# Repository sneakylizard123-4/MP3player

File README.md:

# MP3 Player

A pocket-sized music player I designed and built from scratch. It plays audio off a microSD card, tunes into FM radio, and can record through a MEMS microphone — all on one 50×70mm PCB with an OLED screen, RGB LEDs, and seventeen physical buttons.

It's built around an STM32H743 running at 480MHz, and the audio comes out through a CS43131 DAC. The whole thing was designed in KiCad 10 and the firmware is C++ written with PlatformIO on ST's HAL.

## Why I built this

I wanted a music player that was actually *mine*. Phones sound great and all, but you can't change anything about them — the hardware is sealed up, there's no satisfying button to press, and the software only does what the manufacturer lets it do. I wanted real buttons, a screen, lights that react to the music, and firmware I could rewrite from scratch whenever I felt like it.

It also turned out to be the perfect excuse to practice the stuff I actually enjoy: PCB design, embedded firmware, and getting hardware interfaces to talk to each other.

I went with the STM32H743 because it has the RAM to buffer audio properly, enough peripherals for everything I wanted to add, and 480MHz of headroom so I never have to worry about it being slow.

## Pictures

 | 

## Features

**Audio**

* CS43131 high-res headphone DAC with a built-in amp
* Dedicated low-noise power rail just for the audio stuff
* 3.5mm headphone output
* Si4735 AM/FM radio receiver
* ICS-43434 I2S microphone for recording

**Storage & controls**

* microSD card over 4-bit SDMMC
* OLED display
* 17 buttons: a 3×3 matrix for navigation plus direct controls
* APA102 RGB LEDs

**Sensors**

* LSM6DSL 6-axis IMU
* BME680 temperature / humidity / pressure / gas sensor
* ISL29035 ambient light sensor
* DS3231M real-time clock

**Power**

* USB-C charging via a BQ24090DGQ Li-ion charger
* TPS613222ADBV boost converter for the 5V rail
* Separate digital and low-noise analog rails

## What the sensors actually do

None of these are needed to play music, but they're what turn this from "a box that plays audio" into something that notices the world around it:

* **LSM6DSL IMU** — motion and orientation. You could shake it to skip a track, flip it to mute, rotate the UI, or drive the LEDs off the beat.
* **BME680** — temperature, humidity, pressure, and VOC levels. Nice for showing environmental data on the OLED, and it can track air quality over time.
* **ISL29035** — how bright it is outside. Auto-adjusts the OLED brightness so it stays readable in daylight and saves battery at night.
* **DS3231M RTC** — keeps accurate time even when the player is off, for a clock on the display, recording timestamps, and maybe alarms later.

# Hardware

## Power

A single Li-ion cell powers everything, with separate rails for the digital side, the LEDs, and the analog audio. The charger (BQ24090DGQ) handles USB input, battery management, and has an NTC thermistor on the pack for temperature monitoring plus charge status LEDs. The boost converter (TPS613222ADBV) steps the battery up to 5V for the LEDs and peripherals, a TLV70233 LDO makes the 3.3V digital rail, and a TPS7A4701 low-noise LDO feeds the audio.

Power flow:

```
USB-C
  |
  +-- USBLC6 ESD protection
  |
  +-- BQ24090DGQ Li-ion charger
          |
          +-- Li-ion battery
                  |
                  +-- TPS613222ADBV boost converter
                  |       |
                  |       +-- 5V rail (LEDs and peripherals)
                  |
                  +-- TLV70233 LDO
                  |       |
                  |       +-- 3.3V digital rail
                  |
                  +-- TPS7A4701 low-noise LDO
                          |
                          +-- audio rail
```

The digital and audio rails are deliberately kept apart so switching noise from the boost converter doesn't end up in your headphones. The DAC gets its own clean regulator for the same reason.

## Schematic

The design is split across hierarchical KiCad sheets:

| Sheet        | File                  | Description                                  | Main Components                                        |
| ------------ | --------------------- | -------------------------------------------- | ------------------------------------------------------ |
| Root         | MP3player.kicad_sch   | Connections and system overview              | Power symbols, connectors, mounting holes              |
| STM32 Core   | stm32core.kicad_sch   | MCU and sensors                              | STM32H743, LSM6DSL, BME680, ISL29035, DS3231M          |
| Power        | power.kicad_sch       | Charging and regulation                      | BQ24090DGQ, TPS613222ADBV, TPS7A4701, TLV70233, USBLC6 |
| Audio        | audio.kicad_sch       | Headphone audio path                         | CS43131-CNZR                                           |
| Storage      | storage.kicad_sch     | Removable storage                            | MicroSD socket                                         |
| OLED UI      | oledui.kicad_sch      | Display and buttons                          | OLED, button matrix, GPIO controls                     |
| Radio        | radio.kicad_sch       | AM/FM receiver                               | Si4735-D60-GU                                          |
| Microphone   | microphone.kicad_sch  | Audio input                                  | ICS-43434 MEMS microphone                              |
| LED Spectrum | ledspectrum.kicad_sch | Visual audio display                         | APA102-2020 LEDs                                       |

## PCB

Six layers, 1.6mm thick, about 50×70mm. Internal power planes keep the distribution clean, and I paid attention to keeping the analog audio away from the digital and switching sections. The DAC sits right next to the headphone jack so the analog traces stay short, and the high-current paths around the charger and boost converter are kept tight with proper return paths.

# Assembly

Designed for standard SMT assembly. Here's how it goes together:

1. Apply solder paste with the stencil.
2. Place the small stuff — 0603 resistors and caps, ferrite beads, crystals.
3. Place the big ICs: STM32H743 (LQFP-100), CS43131, Si4735, power management, APA102 LEDs, sensors.
4. Reflow.
5. Check the fine-pitch parts for solder bridges.
6. Install connectors: USB-C, headphone jack, microSD socket, SMA antenna connectors, battery connector, debug headers.
7. Install the user-facing stuff: 17 tactile switches and the OLED connector.
8. Electrical checks — continuity, shorts, and verifying the power rails.
9. Flash the initial firmware over SWD.

## Firmware

The firmware is in `firmware/`, built with PlatformIO on the STM32 HAL. Right now it sets up the hardware: 480MHz clock from the 8MHz crystal via PLL, all the GPIO, the I2C/SPI/UART buses, the SD card interface, and the control pins. The fun part — actual playback, the UI, radio control, recording, and the LED effects — is still being written.

### Build and flash

You'll need PlatformIO (CLI or the VS Code extension) and an ST-Link, CMSIS-DAP, or J-Link debugger.

```bash
cd firmware
pio run
```

To flash over SWD:

```bash
pio run -t upload
```

# Bill of Materials

| Ref      | Part                 | Qty | Package   | Description                         |
| -------- | -------------------- | --- | --------- | ----------------------------------- |
| U4       | STM32H743VIT6        | 1   | LQFP-100  | Main microcontroller                |
| U9       | CS43131-CNZR         | 1   | QFN-40    | Audio DAC                           |
| U10      | Si4735-D60-GU        | 1   | SSOP-24   | FM radio receiver                   |
| MK1      | ICS-43434            | 1   | LGA       | I2S MEMS microphone                 |
| U6       | LSM6DSL              | 1   | LGA-14    | 6-axis IMU                          |
| U8       | BME680               | 1   | LGA-8     | Environmental sensor                |
| U5       | ISL29035             | 1   | DFN-6     | Ambient light sensor                |
| U7       | DS3231M              | 1   | SOIC-16W  | Real-time clock                     |
| U11      | BQ24090DGQ           | 1   | HVSSOP-10 | Li-ion charger                      |
| U12      | TPS613222ADBV        | 1   | SOT-23-5  | Boost converter                     |
| U3       | TPS7A4701xRGW        | 1   | VQFN-20   | Low-noise audio regulator           |
| U2       | TLV70233             | 1   | SOT-23-5  | 3.3V digital regulator              |
| U1       | USBLC6-2SC6          | 1   | SOT-23-6  | USB ESD protection                  |
| D4-D7    | APA102-2020          | 4   | 2×2mm     | RGB LEDs                            |
| D1-D3    | ACDSV6-4448TI-G      | 3   | SOT-363   | Button ESD protection               |
| D10      | BAT54W               | 1   | SOT-323   | Schottky diode                      |
| D8-D9    | 0603 LEDs            | 2   | 0603      | Status LEDs                         |
| J1       | HRO TYPE-C-31-M-12   | 1   | USB-C     | Charging and USB                    |
| J4       | PJ31060-I            | 1   | —         | 3.5mm headphone jack                |
| J5       | Hirose DM3D-SF       | 1   | —         | MicroSD socket                      |
| J6-J7    | Amphenol 901-143     | 2   | SMA       | Antenna connectors                  |
| J2       | JST PH B2B-PH-K      | 1   | 2.0mm     | Battery connector                   |
| J3       | SWD header           | 1   | 2.54mm    | Debug connector                     |
| J8       | OLED header          | 1   | 2.54mm    | Display connector                   |
| L1       | 450µH                | 1   | 0805      | Radio antenna matching              |
| L2       | 2.2µH                | 1   | 0805      | Boost converter inductor            |
| Y1       | 8MHz TXC AA08000002  | 1   | 5032      | MCU crystal                         |
| SW1-SW17 | Tactile switches     | 17  | —         | User controls                       |
| TH1      | 10k NTC              | 1   | 0603      | Battery temperature monitoring      |
| FB1      | 600Ω @100MHz ferrite | 1   | 0603      | Noise filtering                     |

`BOM.csv` has the full BOM with supplier part numbers, links, and pricing.

# Fabrication

Gerbers are in kicad/production/MP3player.zip

Boards and stencils are made through JLCPCB.

PCB specs:

| Specification  | Value         |
| -------------- | ------------- |
| Layers         | 6             |
| Dimensions     | 50×70mm       |
| Thickness      | 1.6mm         |
| Material       | FR-4 TG155    |
| Surface finish | ENIG          |
| Outer copper   | 1oz           |
| Inner copper   | 0.5oz         |
| PCB color      | Purple        |
| Silkscreen     | White         |

Stencil specs:

| Specification         | Value                     |
| --------------------- | ------------------------- |
| Quantity              | 2                         |
| Sides                 | Top and bottom            |
| Manufacturing process | Laser-cut stainless steel |
| Finish                | Electropolished           |
| Coating               | Nano-coating              |

# Known Issues

* Audio performance hasn't been measured with the final firmware yet.
* Battery runtime still needs to be measured.
* RF performance and antenna tuning need real testing.
* Thermal behavior under load hasn't been validated.
* The enclosure design isn't done.

The firmware currently only does hardware init. Remaining features:

* [ ] Audio playback pipeline
* [ ] SD card filesystem support
* [ ] Audio decoding
* [ ] OLED user interface
* [ ] Button handling and debounce
* [ ] Radio control
* [ ] Recording
* [ ] Sensor drivers
* [ ] LED spectrum visualization
* [ ] Battery monitoring

# Credits

* Board, schematics, and firmware designed and written from scratch by me.
* STM32 HAL by STMicroelectronics.
* PlatformIO for firmware builds.
* KiCad libraries for standard symbols and footprints.

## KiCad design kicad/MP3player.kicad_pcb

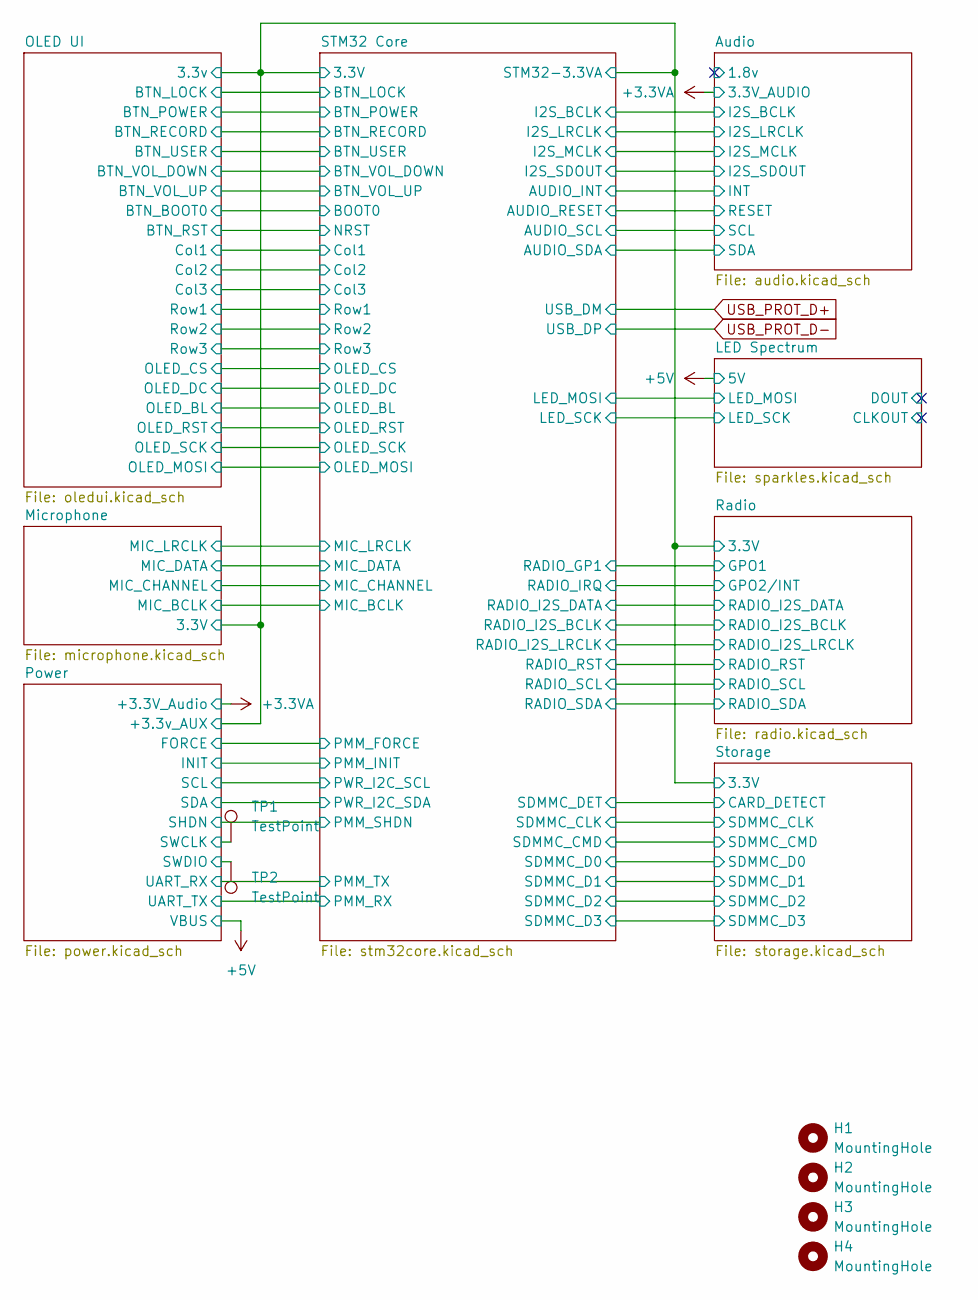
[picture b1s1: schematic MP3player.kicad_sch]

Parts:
H1, H2, H3, H4: MountingHole; MountingHole_3.2mm_M3
TP1, TP2: TestPoint

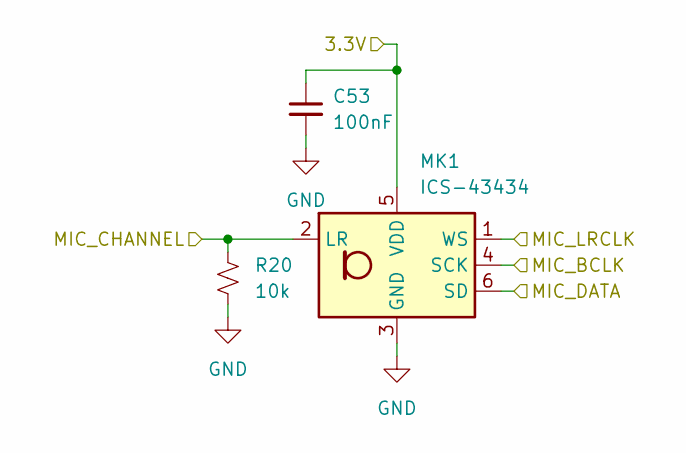
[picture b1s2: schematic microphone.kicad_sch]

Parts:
C53: 100nF; C_0603_1608Metric
MK1: ICS-43434; InvenSense_ICS-43434-6_3.5x2.65mm
R20: 10k; R_0603_1608Metric

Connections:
+3.3V: C53.1, MK1.5 (VDD); also elsewhere on the board
/Microphone/MIC_BCLK: MK1.4 (SCK); also elsewhere on the board
/Microphone/MIC_CHANNEL: MK1.2 (LR), R20.1; also elsewhere on the board
/Microphone/MIC_DATA: MK1.6 (SD); also elsewhere on the board
/Microphone/MIC_LRCLK: MK1.1 (WS); also elsewhere on the board
GND: C53.2, MK1.3 (GND), R20.2; also elsewhere on the board

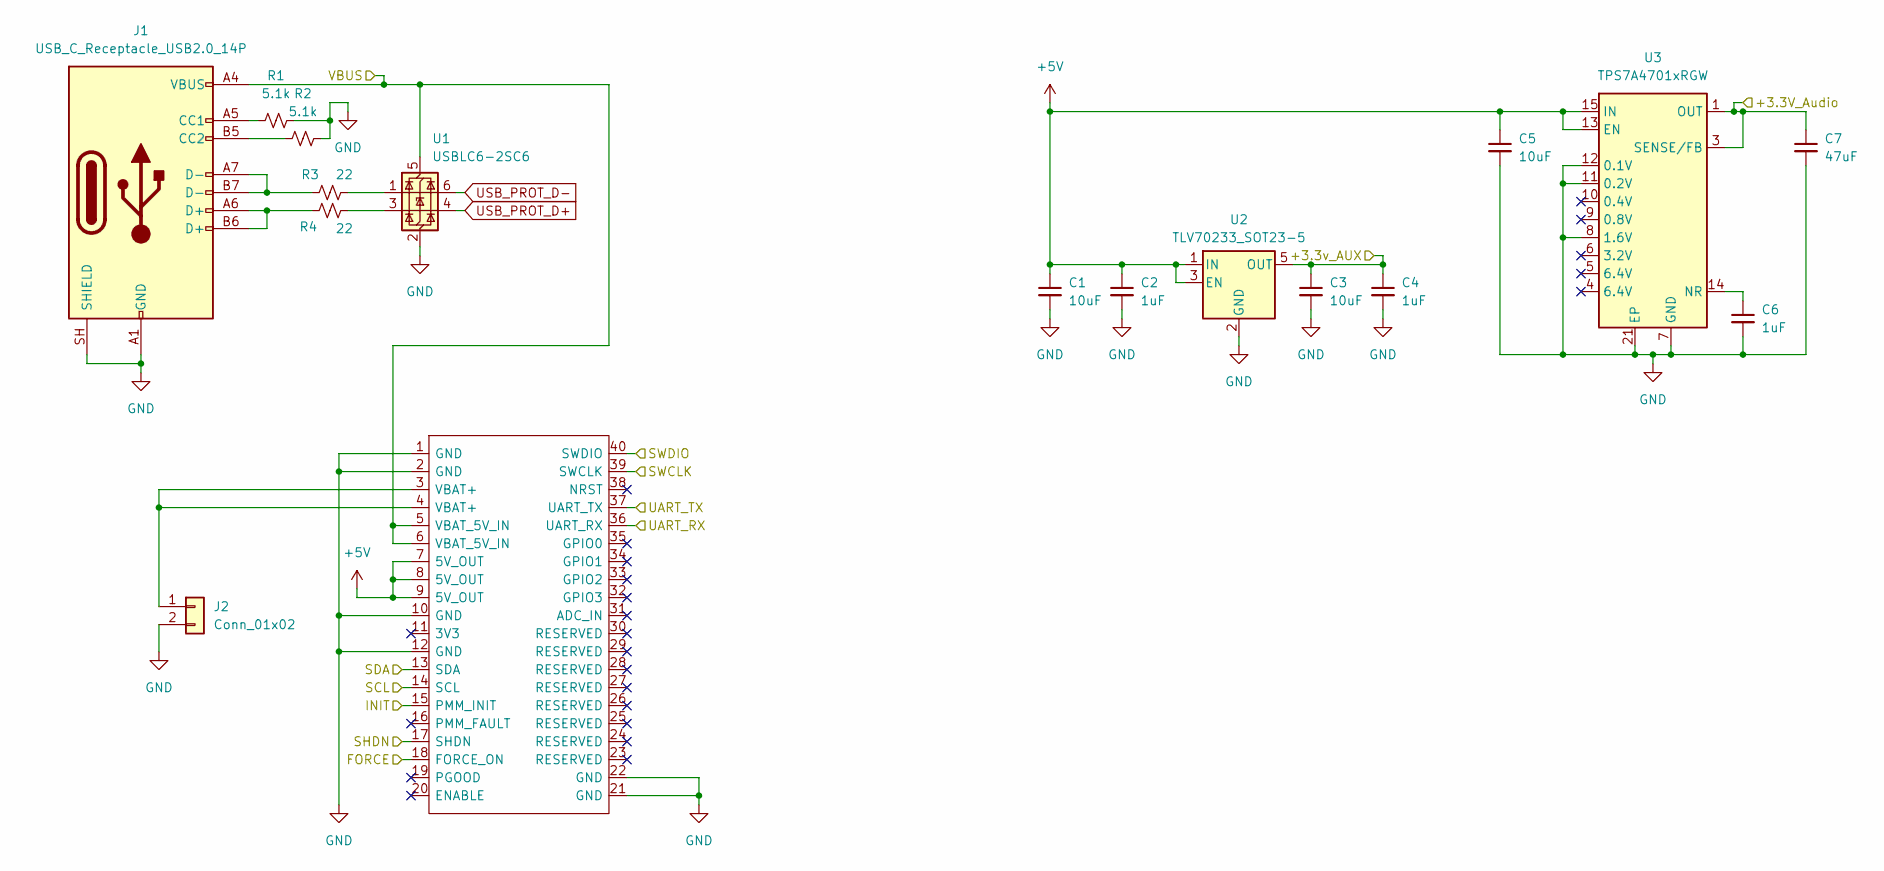
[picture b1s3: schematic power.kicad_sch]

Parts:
A1: PMM
C1, C3, C5: 10uF; C_0603_1608Metric
C2, C4, C6: 1uF; C_0603_1608Metric
C7: 47uF; C_0603_1608Metric
J1: USB_C_Receptacle_USB2.0_14P; USB_C_Receptacle_HRO_TYPE-C-31-M-12
J2: Conn_01x02; JST_PH_B2B-PH-K_1x02_P2.00mm_Vertical
R1, R2: 5.1k
R3, R4: 22
U1: USBLC6-2SC6; SOT-23-6
U2: TLV70233_SOT23-5; SOT-23-5
U3: TPS7A4701xRGW; Texas_RGW0020A_VQFN-20-1EP_5x5mm_P0.65mm_EP3.15x3.15mm_Ther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

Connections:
+3.3V: C3.1, C4.1, U2.5 (OUT); also elsewhere on the board
+3.3VA: C7.1, U3.1 (OUT), U3.3 (SENSE/FB), U3.20 (OUT); also elsewhere on the board
+5V: A1.5 (VBAT_5V_IN), A1.6 (VBAT_5V_IN), A1.7 (5V_OUT), A1.8 (5V_OUT), A1.9 (5V_OUT), C1.1, C2.1, C5.1, J1.A4 (VBUS), J1.A9 (VBUS), J1.B4 (VBUS), J1.B9 (VBUS), U1.5 (VBUS), U2.1 (IN), U2.3 (EN), U3.13 (EN), U3.15 (IN), U3.16 (IN); also elsewhere on the board
+BATT: A1.3 (VBAT+), A1.4 (VBAT+), J2.1; also elsewhere on the board
GND: A1.1 (GND), A1.2 (GND), A1.10 (GND), A1.12 (GND), A1.21 (GND), A1.22 (GND), C1.2, C2.2, C3.2, C4.2, C5.2, C6.2, C7.2, J1.A1 (GND), J1.A12 (GND), J1.B1 (GND), J1.B12 (GND), J1.SH (SHIELD), J2.2, R1.2, R2.2, U1.2 (GND), U2.2 (GND), U3.7 (GND), U3.8 (1.6V), U3.11 (0.2V), U3.12 (0.1V), U3.21 (EP); also elsewhere on the board
unnamed: J1.A5 (CC1), R1.1
unnamed: J1.B5 (CC2), R2.1
unnamed: J1.A6 (D+), J1.B6 (D+), R4.1
unnamed: J1.A7 (D-), J1.B7 (D-), R3.1
unnamed: R3.2, U1.1 (I/O1)
unnamed: R4.2, U1.3 (I/O2)
unnamed: C6.1, U3.14 (NR)
USB_PROT_D+: U1.4 (I/O2); also elsewhere on the board
USB_PROT_D-: U1.6 (I/O1); also elsewhere on the board

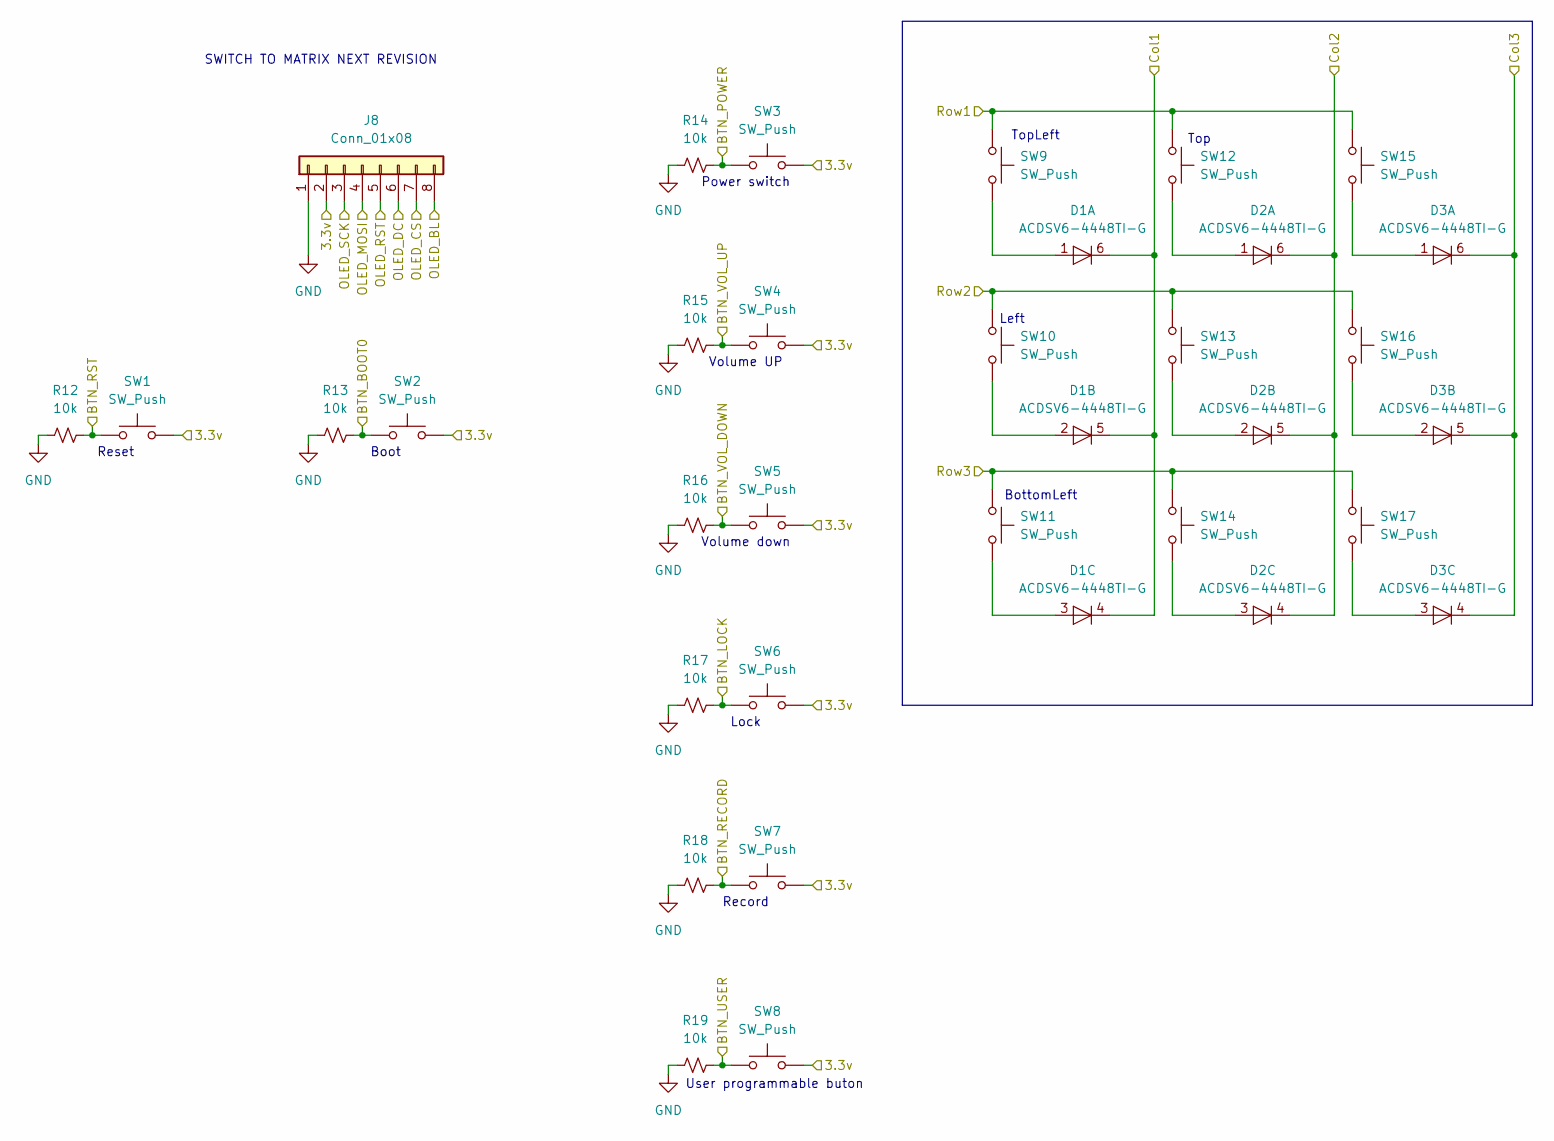
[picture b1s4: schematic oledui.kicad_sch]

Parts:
D1, D2, D3: ACDSV6-4448TI-G; SOT-363_SC-70-6
J8: Conn_01x08; PinHeader_1x08_P2.54mm_Vertical_SMD_Pin1Right
R12, R13, R14, R15, R16, R17, R18, R19: 10k; R_0603_1608Metric
SW1, SW2, SW3, SW4, SW5, SW6, SW7, SW8: SW_Push; Panasonic_EVQPUM_EVQPUD
SW9, SW10, SW11, SW12, SW13, SW14, SW15, SW16, SW17: SW_Push; SW_Push_1P1T_NO_CK_KMR2

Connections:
+3.3V: J8.2, SW1.2, SW2.2, SW3.2, SW4.2, SW5.2, SW6.2, SW7.2, SW8.2; also elsewhere on the board
/OLED UI/BTN_BOOT0: R13.2, SW2.1; also elsewhere on the board
/OLED UI/BTN_LOCK: R17.2, SW6.1; also elsewhere on the board
/OLED UI/BTN_POWER: R14.2, SW3.1; also elsewhere on the board
/OLED UI/BTN_RECORD: R18.2, SW7.1; also elsewhere on the board
/OLED UI/BTN_RST: R12.2, SW1.1; also elsewhere on the board
/OLED UI/BTN_USER: R19.2, SW8.1; also elsewhere on the board
/OLED UI/BTN_VOL_DOWN: R16.2, SW5.1; also elsewhere on the board
/OLED UI/BTN_VOL_UP: R15.2, SW4.1; also elsewhere on the board
/OLED UI/Col1: D1.4 (K), D1.5 (K), D1.6 (K); also elsewhere on the board
/OLED UI/Col2: D2.4 (K), D2.5 (K), D2.6 (K); also elsewhere on the board
/OLED UI/Col3: D3.4 (K), D3.5 (K), D3.6 (K); also elsewhere on the board
/OLED UI/OLED_BL: J8.8; also elsewhere on the board
/OLED UI/OLED_CS: J8.7; also elsewhere on the board
/OLED UI/OLED_DC: J8.6; also elsewhere on the board
/OLED UI/OLED_MOSI: J8.4; also elsewhere on the board
/OLED UI/OLED_RST: J8.5; also elsewhere on the board
/OLED UI/OLED_SCK: J8.3; also elsewhere on the board
/OLED UI/Row1: SW9.1, SW12.1, SW15.1; also elsewhere on the board
/OLED UI/Row2: SW10.1, SW13.1, SW16.1; also elsewhere on the board
/OLED UI/Row3: SW11.1, SW14.1, SW17.1; also elsewhere on the board
GND: J8.1, R12.1, R13.1, R14.1, R15.1, R16.1, R17.1, R18.1, R19.1; also elsewhere on the board
unnamed: D1.1 (A), SW9.2
unnamed: D1.2 (A), SW10.2
unnamed: D1.3 (A), SW11.2
unnamed: D2.1 (A), SW12.2
unnamed: D2.2 (A), SW13.2
unnamed: D2.3 (A), SW14.2
unnamed: D3.1 (A), SW15.2
unnamed: D3.2 (A), SW16.2
unnamed: D3.3 (A), SW17.2

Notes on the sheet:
Record
Top
User programmable buton
SWITCH TO MATRIX NEXT REVISION
BottomLeft
Volume down
Boot
Left
Volume UP
Reset
Power switch
TopLeft
Lock

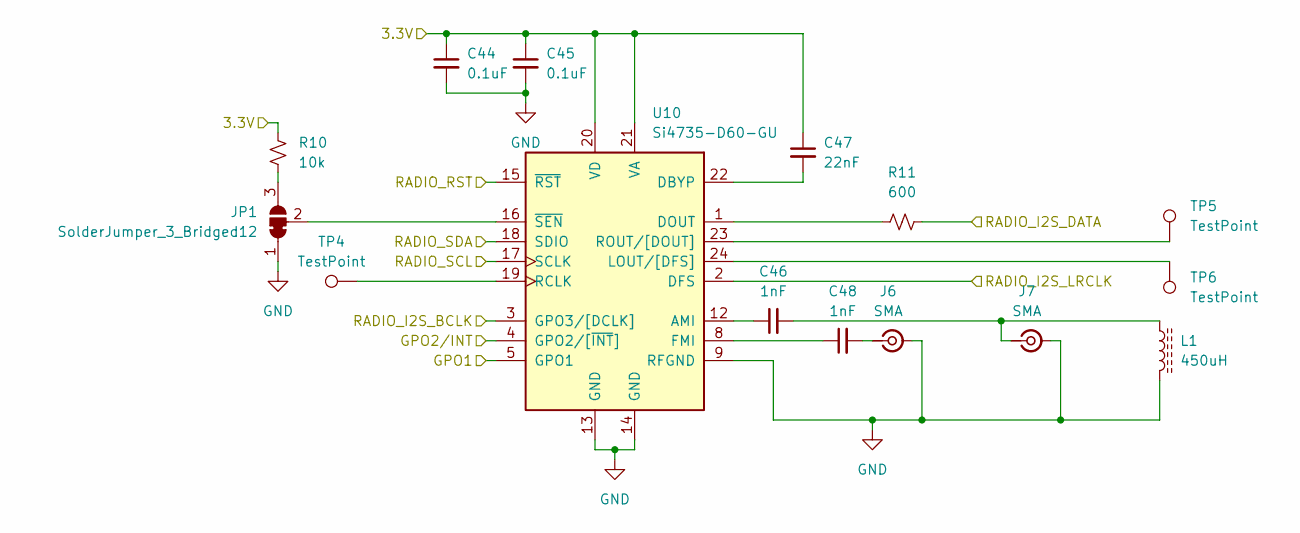
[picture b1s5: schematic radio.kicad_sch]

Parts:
C44, C45: 0.1uF; C_0603_1608Metric
C46, C48: 1nF; C_0603_1608Metric
C47: 22nF; C_0603_1608Metric
J6, J7: SMA; SMA_Amphenol_901-143_Horizontal
JP1: SolderJumper_3_Bridged12; SolderJumper-3_P1.3mm_Bridged12_RoundedPad1.0x1.5mm
L1: 450uH; L_1206_3216Metric
R10: 10k; R_0603_1608Metric
R11: 600; R_0603_1608Metric
TP4, TP5, TP6: TestPoint; TestPoint_Pad_D1.5mm
U10: Si4735-D60-GU; SSOP-24_3.9x8.7mm_P0.635mm

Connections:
+3.3V: C44.1, C45.1, C47.1, R10.2, U10.20 (VD), U10.21 (VA); also elsewhere on the board
/Radio/GPO1: U10.5 (GPO1); also elsewhere on the board
/Radio/GPO2/INT: U10.4 (GPO2/[~INT]); also elsewhere on the board
/Radio/RADIO_I2S_BCLK: U10.3 (GPO3/[DCLK]); also elsewhere on the board
/Radio/RADIO_I2S_DATA: R11.2; also elsewhere on the board
/Radio/RADIO_I2S_LRCLK: U10.2 (DFS); also elsewhere on the board
/Radio/RADIO_RST: U10.15 (~RST); also elsewhere on the board
/Radio/RADIO_SCL: U10.17 (SCLK); also elsewhere on the board
/Radio/RADIO_SDA: U10.18 (SDIO); also elsewhere on the board
GND: C44.2, C45.2, J6.2 (Ext), J7.2 (Ext), JP1.1 (A), L1.2, U10.9 (RFGND), U10.13 (GND), U10.14 (GND); also elsewhere on the board
unnamed: C48.2, J6.1 (In)
unnamed: C46.2, J7.1 (In), L1.1
unnamed: JP1.3 (B), R10.1
unnamed: JP1.2 (C), U10.16 (~SEN)
unnamed: C46.1, U10.12 (AMI)
unnamed: C47.2, U10.22 (DBYP)
unnamed: R11.1, U10.1 (DOUT)
unnamed: C48.1, U10.8 (FMI)
unnamed: TP6.1 (1_1), U10.24 (LOUT/[DFS])
unnamed: TP4.1 (1_1), U10.19 (RCLK)
unnamed: TP5.1 (1_1), U10.23 (ROUT/[DOUT])

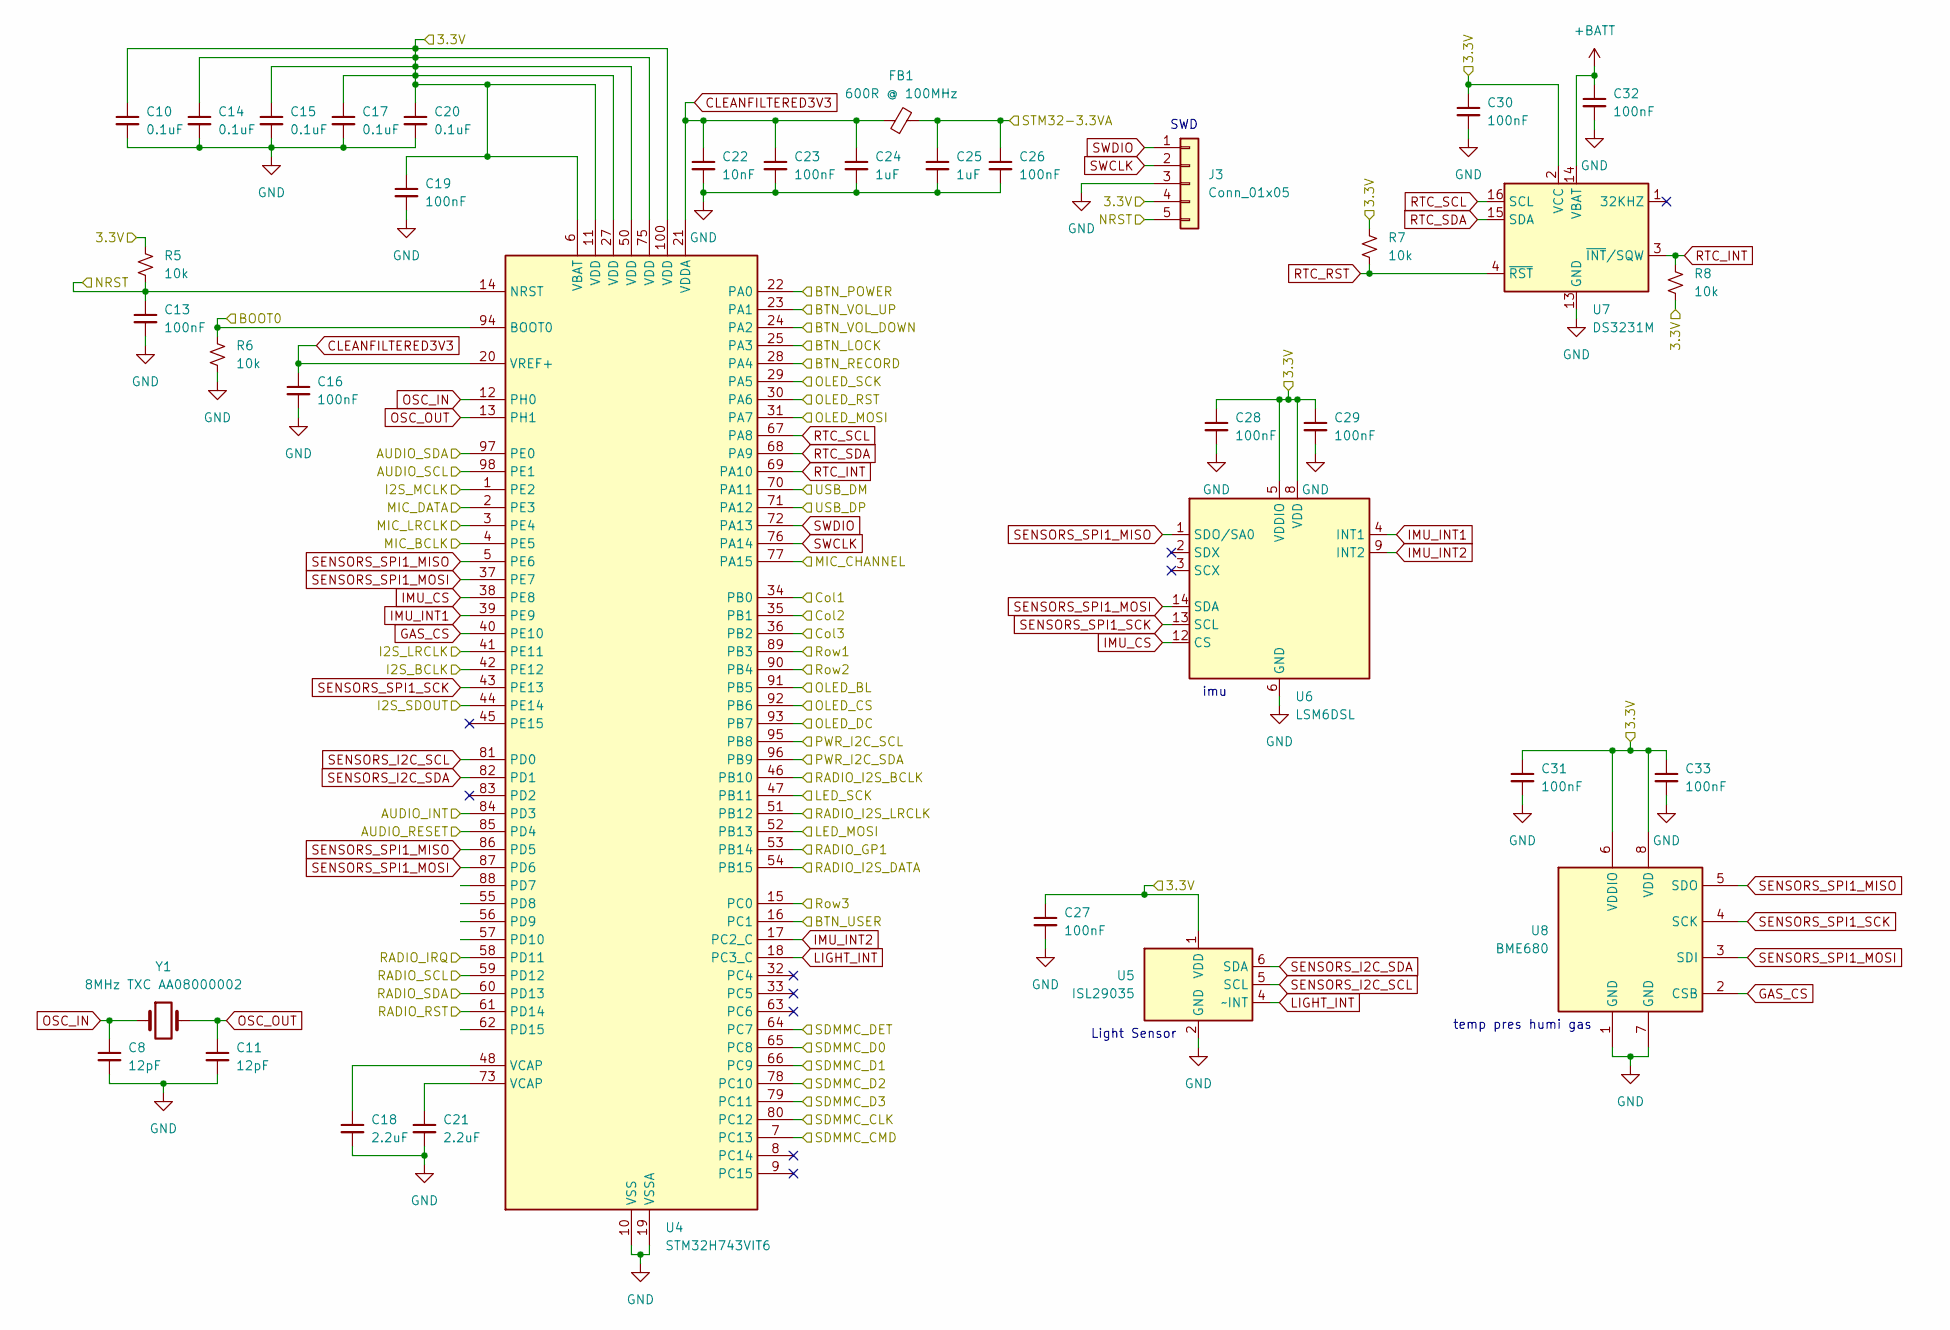
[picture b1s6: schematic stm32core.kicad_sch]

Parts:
C8, C11: 12pF; C_0603_1608Metric
C10, C14, C15, C17, C20: 0.1uF; C_0603_1608Metric
C13, C16, C19, C23, C26, C27, C28, C29, C30, C31, C32, C33: 100nF; C_0603_1608Metric
C18, C21: 2.2uF; C_0603_1608Metric
C22: 10nF; C_0603_1608Metric
C24, C25: 1uF; C_0603_1608Metric
FB1: 600R @ 100MHz; L_0603_1608Metric
J3: Conn_01x05; PinHeader_1x05_P2.54mm_Vertical
R5, R6, R7, R8: 10k; R_0603_1608Metric
U4: STM32H743VIT6; LQFP-100_14x14mm_P0.5mm
U5: ISL29035; Renesas_DFN-6_1.5x1.6mm_P0.5mm
U6: LSM6DSL; LGA-14_3x2.5mm_P0.5mm_LayoutBorder3x4y
U7: DS3231M; SOIC-16W_7.5x10.3mm_P1.27mm
U8: BME680; Bosch_LGA-8_3x3mm_P0.8mm_ClockwisePinNumbering
Y1: 8MHz TXC AA08000002; Crystal_SMD_5032-2Pin_5.0x3.2mm

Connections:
+3.3V: C10.1, C14.1, C15.1, C17.1, C19.1, C20.1, C25.1, C26.1, C27.1, C28.1, C29.1, C30.1, C31.1, C33.1, FB1.2, J3.4, R5.1, R7.1, R8.2, U4.6 (VBAT), U4.11 (VDD), U4.27 (VDD), U4.50 (VDD), U4.75 (VDD), U4.100 (VDD), U5.1 (VDD), U6.5 (VDDIO), U6.8 (VDD), U7.2 (VCC), U8.6 (VDDIO), U8.8 (VDD); also elsewhere on the board
+BATT: C32.1, U7.14 (VBAT); also elsewhere on the board
/Audio/I2S_BCLK: U4.42 (PE12); also elsewhere on the board
/Audio/I2S_LRCLK: U4.41 (PE11); also elsewhere on the board
/Audio/I2S_MCLK: U4.1 (PE2); also elsewhere on the board
/Audio/I2S_SDOUT: U4.44 (PE14); also elsewhere on the board
/Audio/INT: U4.84 (PD3); also elsewhere on the board
/Audio/RESET: U4.85 (PD4); also elsewhere on the board
/Audio/SCL: U4.98 (PE1); also elsewhere on the board
/Audio/SDA: U4.97 (PE0); also elsewhere on the board
/LED Spectrum/LED_MOSI: U4.52 (PB13); also elsewhere on the board
/LED Spectrum/LED_SCK: U4.47 (PB11); also elsewhere on the board
/Microphone/MIC_BCLK: U4.4 (PE5); also elsewhere on the board
/Microphone/MIC_CHANNEL: U4.77 (PA15); also elsewhere on the board
/Microphone/MIC_DATA: U4.2 (PE3); also elsewhere on the board
/Microphone/MIC_LRCLK: U4.3 (PE4); also elsewhere on the board
/OLED UI/BTN_BOOT0: R6.1, U4.94 (BOOT0); also elsewhere on the board
/OLED UI/BTN_LOCK: U4.25 (PA3); also elsewhere on the board
/OLED UI/BTN_POWER: U4.22 (PA0); also elsewhere on the board
/OLED UI/BTN_RECORD: U4.28 (PA4); also elsewhere on the board
/OLED UI/BTN_RST: C13.1, J3.5, R5.2, U4.14 (NRST); also elsewhere on the board
/OLED UI/BTN_USER: U4.16 (PC1); also elsewhere on the board
/OLED UI/BTN_VOL_DOWN: U4.24 (PA2); also elsewhere on the board
/OLED UI/BTN_VOL_UP: U4.23 (PA1); also elsewhere on the board
/OLED UI/Col1: U4.34 (PB0); also elsewhere on the board
/OLED UI/Col2: U4.35 (PB1); also elsewhere on the board
/OLED UI/Col3: U4.36 (PB2); also elsewhere on the board
/OLED UI/OLED_BL: U4.91 (PB5); also elsewhere on the board
/OLED UI/OLED_CS: U4.92 (PB6); also elsewhere on the board
/OLED UI/OLED_DC: U4.93 (PB7); also elsewhere on the board
/OLED UI/OLED_MOSI: U4.31 (PA7); also elsewhere on the board
/OLED UI/OLED_RST: U4.30 (PA6); also elsewhere on the board
/OLED UI/OLED_SCK: U4.29 (PA5); also elsewhere on the board
/OLED UI/Row1: U4.89 (PB3); also elsewhere on the board
/OLED UI/Row2: U4.90 (PB4); also elsewhere on the board
/OLED UI/Row3: U4.15 (PC0); also elsewhere on the board
/Radio/GPO1: U4.53 (PB14); also elsewhere on the board
/Radio/GPO2/INT: U4.58 (PD11); also elsewhere on the board
/Radio/RADIO_I2S_BCLK: U4.46 (PB10); also elsewhere on the board
/Radio/RADIO_I2S_DATA: U4.54 (PB15); also elsewhere on the board
/Radio/RADIO_I2S_LRCLK: U4.51 (PB12); also elsewhere on the board
/Radio/RADIO_RST: U4.61 (PD14); also elsewhere on the board
/Radio/RADIO_SCL: U4.59 (PD12); also elsewhere on the board
/Radio/RADIO_SDA: U4.60 (PD13); also elsewhere on the board
/STM32 Core/PWR_I2C_SCL: U4.95 (PB8)
/STM32 Core/PWR_I2C_SDA: U4.96 (PB9)
/STM32 Core/SDMMC_CLK: U4.80 (PC12); also elsewhere on the board
/STM32 Core/SDMMC_CMD: U4.7 (PC13); also elsewhere on the board
/STM32 Core/SDMMC_D0: U4.65 (PC8); also elsewhere on the board
/STM32 Core/SDMMC_D1: U4.66 (PC9); also elsewhere on the board
/STM32 Core/SDMMC_D2: U4.78 (PC10); also elsewhere on the board
/STM32 Core/SDMMC_D3: U4.79 (PC11); also elsewhere on the board
/STM32 Core/SDMMC_DET: U4.64 (PC7); also elsewhere on the board
CLEANFILTERED3V3: C16.1, C22.1, C23.1, C24.1, FB1.1, U4.20 (VREF+), U4.21 (VDDA)
GAS_CS: U4.40 (PE10), U8.2 (CSB)
GND: C8.2, C10.2, C11.2, C13.2, C14.2, C15.2, C16.2, C17.2, C18.2, C19.2, C20.2, C21.2, C22.2, C23.2, C24.2, C25.2, C26.2, C27.2, C28.2, C29.2, C30.2, C31.2, C32.2, C33.2, J3.3, R6.2, U4.10 (VSS), U4.19 (VSSA), U4.26 (VSS), U4.49 (VSS), U4.74 (VSS), U4.99 (VSS), U5.2 (GND), U6.6 (GND), U6.7 (GND), U7.5 (GND), U7.6 (GND), U7.7 (GND), U7.8 (GND), U7.9 (GND), U7.10 (GND), U7.11 (GND), U7.12 (GND), U7.13 (GND), U8.1 (GND), U8.7 (GND); also elsewhere on the board
IMU_CS: U4.38 (PE8), U6.12 (CS)
IMU_INT1: U4.39 (PE9), U6.4 (INT1)
IMU_INT2: U4.17 (PC2_C), U6.9 (INT2)
LIGHT_INT: U4.18 (PC3_C), U5.4 (~INT)
unnamed: C18.1, U4.48 (VCAP)
unnamed: C21.1, U4.73 (VCAP)
OSC_IN: C8.1, U4.12 (PH0), Y1.1
OSC_OUT: C11.1, U4.13 (PH1), Y1.2
RTC_INT: R8.1, U4.69 (PA10), U7.3 (~INT/SQW)
RTC_RST: R7.2, U7.4 (~RST)
RTC_SCL: U4.67 (PA8), U7.16 (SCL)
RTC_SDA: U4.68 (PA9), U7.15 (SDA)
SENSORS_I2C_SCL: U4.81 (PD0), U5.5 (SCL)
SENSORS_I2C_SDA: U4.82 (PD1), U5.6 (SDA)
SENSORS_SPI1_MISO: U4.5 (PE6), U4.86 (PD5), U6.1 (SDO/SA0), U8.5 (SDO)
SENSORS_SPI1_MOSI: U4.37 (PE7), U4.87 (PD6), U6.14 (SDA), U8.3 (SDI)
SENSORS_SPI1_SCK: U4.43 (PE13), U6.13 (SCL), U8.4 (SCK)
SWCLK: J3.2, U4.76 (PA14)
SWDIO: J3.1, U4.72 (PA13)
USB_PROT_D+: U4.70 (PA11); also elsewhere on the board
USB_PROT_D-: U4.71 (PA12); also elsewhere on the board

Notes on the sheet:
SWD
temp pres humi gas
Light Sensor
imu

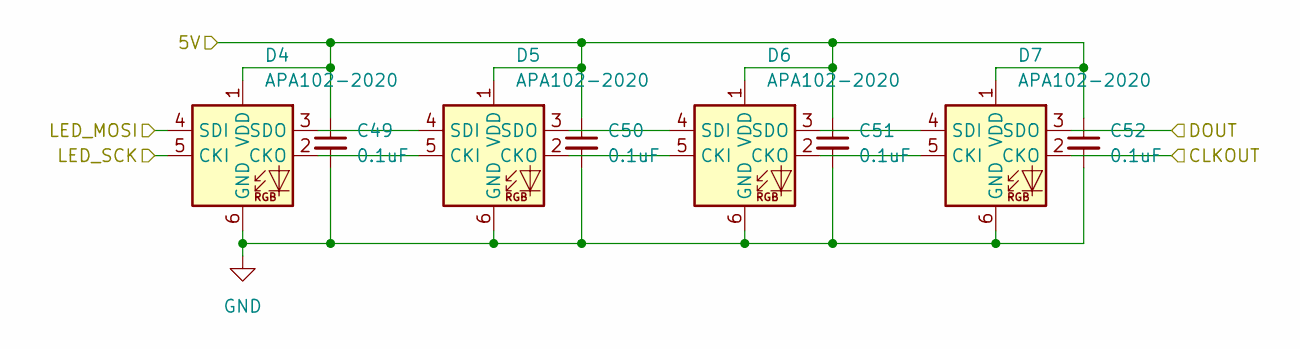
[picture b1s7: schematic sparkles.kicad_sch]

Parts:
C49, C50, C51, C52: 0.1uF; C_0603_1608Metric
D4, D5, D6, D7: APA102-2020; LED-APA102-2020

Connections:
+5V: C49.1, C50.1, C51.1, C52.1, D4.1 (VDD), D5.1 (VDD), D6.1 (VDD), D7.1 (VDD); also elsewhere on the board
/LED Spectrum/CLKOUT: D7.2 (CKO)
/LED Spectrum/DOUT: D7.3 (SDO)
/LED Spectrum/LED_MOSI: D4.4 (SDI); also elsewhere on the board
/LED Spectrum/LED_SCK: D4.5 (CKI); also elsewhere on the board
GND: C49.2, C50.2, C51.2, C52.2, D4.6 (GND), D5.6 (GND), D6.6 (GND), D7.6 (GND); also elsewhere on the board
unnamed: D4.2 (CKO), D5.5 (CKI)
unnamed: D4.3 (SDO), D5.4 (SDI)
unnamed: D5.2 (CKO), D6.5 (CKI)
unnamed: D5.3 (SDO), D6.4 (SDI)
unnamed: D6.2 (CKO), D7.5 (CKI)
unnamed: D6.3 (SDO), D7.4 (SDI)

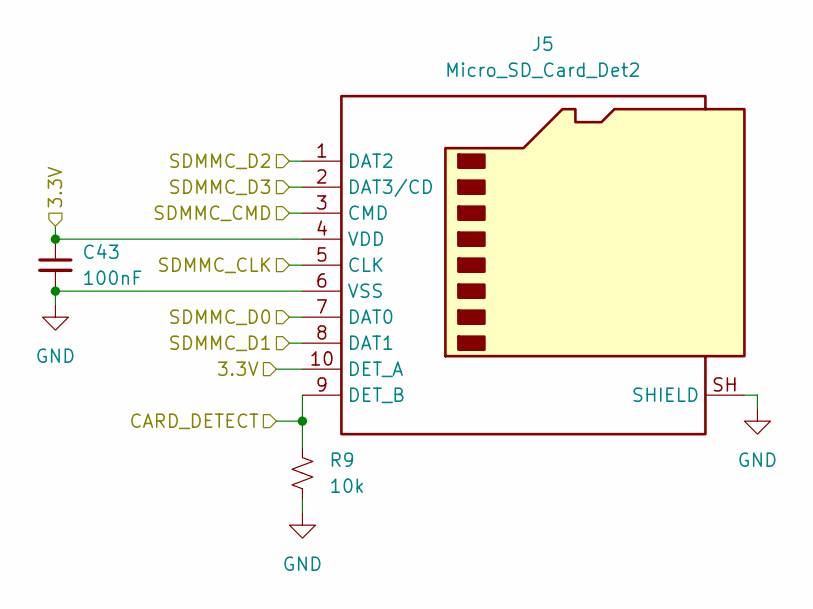
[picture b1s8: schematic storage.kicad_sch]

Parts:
C43: 100nF; C_0603_1608Metric
J5: Micro_SD_Card_Det2; microSD_HC_Hirose_DM3D-SF
R9: 10k; R_0603_1608Metric

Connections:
+3.3V: C43.1, J5.4 (VDD), J5.10 (DET_A); also elsewhere on the board
/STM32 Core/SDMMC_CLK: J5.5 (CLK); also elsewhere on the board
/STM32 Core/SDMMC_CMD: J5.3 (CMD); also elsewhere on the board
/STM32 Core/SDMMC_D0: J5.7 (DAT0); also elsewhere on the board
/STM32 Core/SDMMC_D1: J5.8 (DAT1); also elsewhere on the board
/STM32 Core/SDMMC_D2: J5.1 (DAT2); also elsewhere on the board
/STM32 Core/SDMMC_D3: J5.2 (DAT3/CD); also elsewhere on the board
/STM32 Core/SDMMC_DET: J5.9 (DET_B), R9.1; also elsewhere on the board
GND: C43.2, J5.6 (VSS), J5.SH (SHIELD), R9.2; also elsewhere on the board

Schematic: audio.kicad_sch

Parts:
C34, C35, C41: 100nF; C_0603_1608Metric
C36, C37: 15uF; C_0603_1608Metric
C38, C39, C40: 2.2uF; C_0603_1608Metric
C42: 4.7uF; C_0603_1608Metric
J4: AudioJack3_Ground_SwitchTR; Jack_3.5mm_PJ31060-I_Horizontal
TP3: TestPoint; TestPoint_Pad_D1.5mm
U9: CS43131-CNZR; TQFN-40-1EP_5x5mm_P0.4mm_EP3.5x3.5mm; MPN CS43131-CNZR; LCSC Part C965907

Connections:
+3.3VA: C41.1, C42.1, U9.26 (VP); also elsewhere on the board
/Audio/1.8v: C34.1, C35.1, C36.2, C40.1, U9.4 (VD), U9.7 (VA), U9.25 (VCP), U9.31 (VL); also elsewhere on the board
/Audio/I2S_BCLK: U9.34 (SCLK1); also elsewhere on the board
/Audio/I2S_LRCLK: U9.38 (LRCK1); also elsewhere on the board
/Audio/I2S_MCLK: U9.37 (XTI/MCLK); also elsewhere on the board
/Audio/I2S_SDOUT: U9.2 (SDIN1); also elsewhere on the board
/Audio/INT: U9.27 (~INT); also elsewhere on the board
/Audio/RESET: U9.28 (~RESET); also elsewhere on the board
/Audio/SCL: U9.1 (SCL); also elsewhere on the board
/Audio/SDA: U9.39 (SDA); also elsewhere on the board
/Audio/VCP_FILT/FLYC_VCP: U9.23 (FLYC_VCP); also elsewhere on the board
/Audio/VCP_FILT/FLYN_VCP: U9.20 (FLYN_VCP); also elsewhere on the board
/Audio/VCP_FILT/FLYP_VCP: U9.24 (FLYP_VCP); also elsewhere on the board
/Audio/VCP_FILT/GNDCP: U9.19 (GNDCP); also elsewhere on the board
/Audio/VCP_FILT/VCP_FILT+: U9.21 (VCP_FILT+); also elsewhere on the board
/Audio/VCP_FILT/VCP_FILT-: U9.18 (VCP_FILT–); also elsewhere on the board
GND: C34.2, C35.2, C39.2, C40.2, C41.2, C42.2, J4.1, J4.2, U9.8 (GNDA), U9.13 (HPREFA), U9.17 (HPREFB), U9.30 (ADR), U9.35 (GNDD), U9.36 (XTO), U9.41 (EP); also elsewhere on the board
unnamed: C37.1, C39.1, U9.9 (-VA)
unnamed: TP3.1 (1_1), U9.33 (CLKOUT)
unnamed: C36.1, U9.5 (FILT+)
unnamed: C37.2, U9.6 (FILT–)
unnamed: C38.2, U9.11 (FLYN_VA)
unnamed: C38.1, U9.10 (FLYP_VA)
unnamed: J4.4, U9.14 (HPOUTA)
unnamed: J4.3, U9.16 (HPOUTB)
unnamed: J4.6, U9.22 (HP_DETECT)

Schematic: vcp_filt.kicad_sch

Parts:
C54, C55, C56, C57, C58: 2.2uF; C_0603_1608Metric

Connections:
/Audio/1.8v: C58.1; also elsewhere on the board
/Audio/VCP_FILT/FLYC_VCP: C55.2, C56.1; also elsewhere on the board
/Audio/VCP_FILT/FLYN_VCP: C56.2; also elsewhere on the board
/Audio/VCP_FILT/FLYP_VCP: C55.1; also elsewhere on the board
/Audio/VCP_FILT/GNDCP: C54.2, C57.2, C58.2; also elsewhere on the board
/Audio/VCP_FILT/VCP_FILT+: C57.1; also elsewhere on the board
/Audio/VCP_FILT/VCP_FILT-: C54.1; also elsewhere on the board
